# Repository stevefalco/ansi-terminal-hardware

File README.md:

ANSI Terminal is a "dumb" terminal that emulates part of a VT100.  It is sufficient to use with vi under 2.11bsd, and it also works well as a dumb terminal for Linux.  It successfully allows editing using the "vim" editor.  An M68K (M68000) soft-core processor is contained in an FPGA on a CYC1000 module, and handles all the processing chores.

This project contains IP cores as follows:

https://github.com/ijor/fx68k provides the M68000 processor.

https://opencores.org/projects/a_vhd_16550_uart provides a 16550 compatible uart.

Unlike many existing terminal projects, this project targets 1280x1024 monitors, which are much more common than the 640x480 monitors of days gone by.  This also allows higher quality characters, using 16x32 glyphs, rather than the more common 8x16 glyphs.

The terminal supports both hardware and software flow control, as selected by a dip switch, and baud rates from 110 to 115200 are supported.

This project contains the KiCAD schematic, board layout, gerbers, and a 3-D printable case design.  Note that this is a 2-layer board with surface mount components.

A companion project, https://github.com/stevefalco/ansi-terminal-firmware contains the FPGA and assembly language software for the ANSI Terminal.

Here are photos of the case, pcb, schematic and displayed text.  There is a higher resolution copy of the schematic in file terminal.pdf.

ANSI Terminal

(c) 2021 Steven A. Falco

ANSI Terminal is free software: you can redistribute it and/or modify
it under the terms of the GNU General Public License as published by
the Free Software Foundation, either version 3 of the License, or
(at your option) any later version.

ANSI Terminal is distributed in the hope that it will be useful,
but WITHOUT ANY WARRANTY; without even the implied warranty of
MERCHANTABILITY or FITNESS FOR A PARTICULAR PURPOSE.  See the
GNU General Public License for more details.

You should have received a copy of the GNU General Public License
along with ANSI Terminal.  If not, see <https://www.gnu.org/licenses/>.

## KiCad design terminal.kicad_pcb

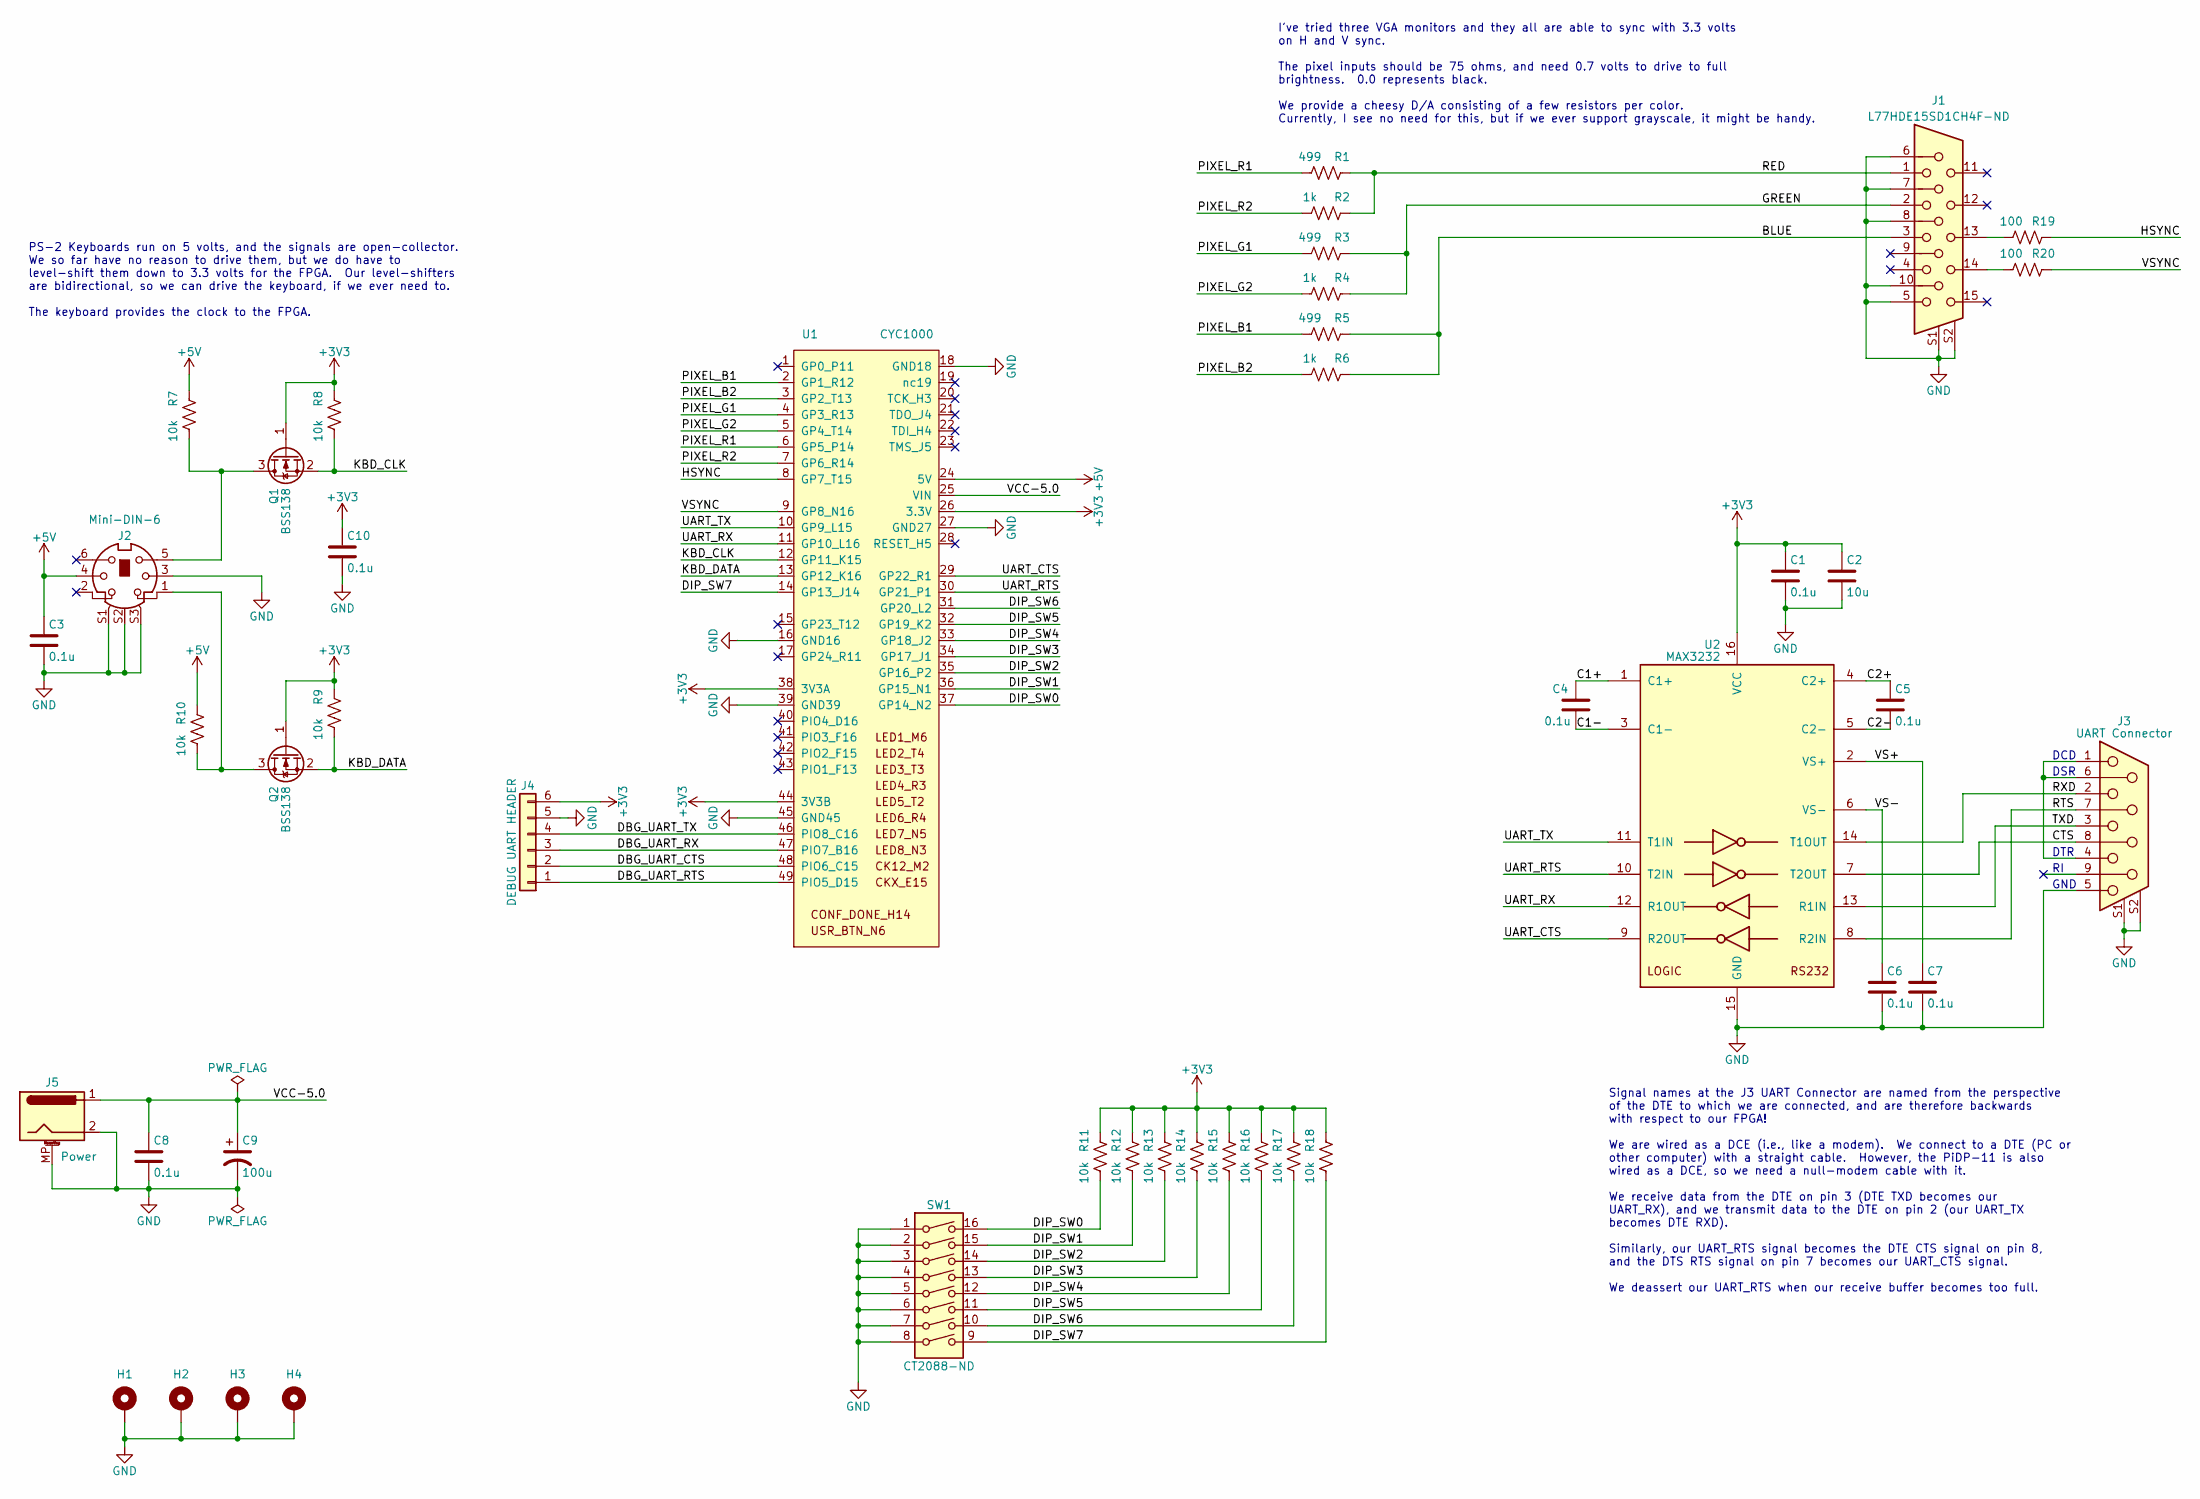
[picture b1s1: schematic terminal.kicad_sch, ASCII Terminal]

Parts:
C1, C3, C4, C5, C6, C7, C8, C10: 0.1u; C_0603_1608Metric_Pad1.08x0.95mm_HandSolder
C2: 10u; C_0603_1608Metric_Pad1.08x0.95mm_HandSolder
C9: 100u; C_1210_3225Metric_Pad1.33x2.70mm_HandSolder
H1, H2, H3, H4: MountingHole_Pad; MountingHole_3.2mm_M3_DIN965_Pad
J1: L77HDE15SD1CH4F-ND; AMPHENOL_L77HDE15SD1CH4F
J2: Mini-DIN-6; CUI_MD-60SM
J3: UART Connector; AMPHENOL_LD09S33E4GX00LF
J4: DEBUG UART HEADER; PinHeader_1x06_P2.54mm_Vertical
J5: Power; BarrelJack_CUI_PJ-063AH_Horizontal
Q1, Q2: BSS138; SOT-23
R1, R3, R5: 499; R_0603_1608Metric_Pad0.98x0.95mm_HandSolder
R2, R4, R6: 1k; R_0603_1608Metric_Pad0.98x0.95mm_HandSolder
R7, R8, R9, R10, R11, R12, R13, R14, R15, R16, R17, R18: 10k; R_0603_1608Metric_Pad0.98x0.95mm_HandSolder
R19, R20: 100; R_0603_1608Metric_Pad0.98x0.95mm_HandSolder
SW1: CT2088-ND; DIP-16_W7.62mm_Socket
U1: CYC1000
U2: MAX3232; TSSOP-16_4.4x5mm_P0.65mm

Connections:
+3V3: C1.1, C2.1, C10.1, J4.6, Q1.1 (G), Q2.1 (G), R8.1, R9.1, R11.1, R12.1, R13.1, R14.1, R15.1, R16.1, R17.1, R18.1, U1.26 (3.3V), U1.38 (3V3A), U1.44 (3V3B), U2.16 (VCC)
+5V: C3.1, J2.4, R7.1, R10.1, U1.24 (5V)
/BLUE: J1.3, R5.1, R6.1
/C1+: C4.1, U2.1 (C1+)
/C1-: C4.2, U2.3 (C1-)
/C2+: C5.1, U2.4 (C2+)
/C2-: C5.2, U2.5 (C2-)
/CTS: J3.8, U2.7 (T2OUT)
/DBG_UART_CTS: J4.2, U1.48 (PIO6_C15)
/DBG_UART_RTS: J4.1, U1.49 (PIO5_D15)
/DBG_UART_RX: J4.3, U1.47 (PIO7_B16)
/DBG_UART_TX: J4.4, U1.46 (PIO8_C16)
/DIP_SW0: R11.2, SW1.16, U1.37 (GP14_N2)
/DIP_SW1: R12.2, SW1.15, U1.36 (GP15_N1)
/DIP_SW2: R13.2, SW1.14, U1.35 (GP16_P2)
/DIP_SW3: R14.2, SW1.13, U1.34 (GP17_J1)
/DIP_SW4: R15.2, SW1.12, U1.33 (GP18_J2)
/DIP_SW5: R16.2, SW1.11, U1.32 (GP19_K2)
/DIP_SW6: R17.2, SW1.10, U1.31 (GP20_L2)
/DIP_SW7: R18.2, SW1.9, U1.14 (GP13_J14)
/GREEN: J1.2, R3.1, R4.1
/HSYNC: R19.1, U1.8 (GP7_T15)
/KBD_CLK: Q1.2 (S), R8.2, U1.12 (GP11_K15)
/KBD_DATA: Q2.2 (S), R9.2, U1.13 (GP12_K16)
/PIXEL_B1: R5.2, U1.2 (GP1_R12)
/PIXEL_B2: R6.2, U1.3 (GP2_T13)
/PIXEL_G1: R3.2, U1.4 (GP3_R13)
/PIXEL_G2: R4.2, U1.5 (GP4_T14)
/PIXEL_R1: R1.2, U1.6 (GP5_P14)
/PIXEL_R2: R2.2, U1.7 (GP6_R14)
/RED: J1.1, R1.1, R2.1
/RTS: J3.7, U2.8 (R2IN)
/RXD: J3.2, U2.14 (T1OUT)
/TXD: J3.3, U2.13 (R1IN)
/UART_CTS: U1.29 (GP22_R1), U2.9 (R2OUT)
/UART_RTS: U1.30 (GP21_P1), U2.10 (T2IN)
/UART_RX: U1.11 (GP10_L16), U2.12 (R1OUT)
/UART_TX: U1.10 (GP9_L15), U2.11 (T1IN)
/VCC-5.0: C8.1, C9.1, J5.1, U1.25 (VIN)
/VS+: C7.1, U2.2 (VS+)
/VS-: C6.1, U2.6 (VS-)
/VSYNC: R20.1, U1.9 (GP8_N16)
GND: C1.2, C2.2, C3.2, C6.2, C7.2, C8.2, C9.2, C10.2, H1.1, H2.1, H3.1, H4.1, J1.5, J1.6, J1.7, J1.8, J1.10, J1.S1, J1.S2, J2.3, J2.S1, J2.S2, J2.S3, J3.5, J3.S1, J3.S2, J4.5, J5.2, J5.MP (MountPin), SW1.1, SW1.2, SW1.3, SW1.4, SW1.5, SW1.6, SW1.7, SW1.8, U1.16 (GND16), U1.18 (GND18), U1.27 (GND27), U1.39 (GND39), U1.45 (GND45), U2.15 (GND)
unnamed: J1.13, R19.2
unnamed: J1.14, R20.2
unnamed: J2.1, Q2.3 (D), R10.2
unnamed: J2.5, Q1.3 (D), R7.2
unnamed: J3.1, J3.4, J3.6

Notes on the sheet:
GND
Signal names at the J3 UART Connector are named from the perspective of the DTE to which we are connected, and are therefore backwards with respect to our FPGA! We are wired as a DCE (i.e., like a modem). We connect to a DTE (PC or other computer) with a straight cable. However, the PiDP-11 is also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
DTR
I've tried three VGA monitors and they all are able to sync with 3.3 volts on H and V sync. The pixel inputs should be 75 ohms, and need 0.7 volts to drive to full brightness. 0.0 represents black. We provide a cheesy D/A consisting of a few resistors per color. Currently, I see no need for this, b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
PS-2 Keyboards run on 5 volts, and the signals are open-collector. We so far have no reason to drive them, but we do have to level-shift them down to 3.3 volts for the FPGA. Our level-shifters are bidirectional, so we can drive the keyboard, if we ever need to. The keyboard provides the clock to th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
DCD
DSR

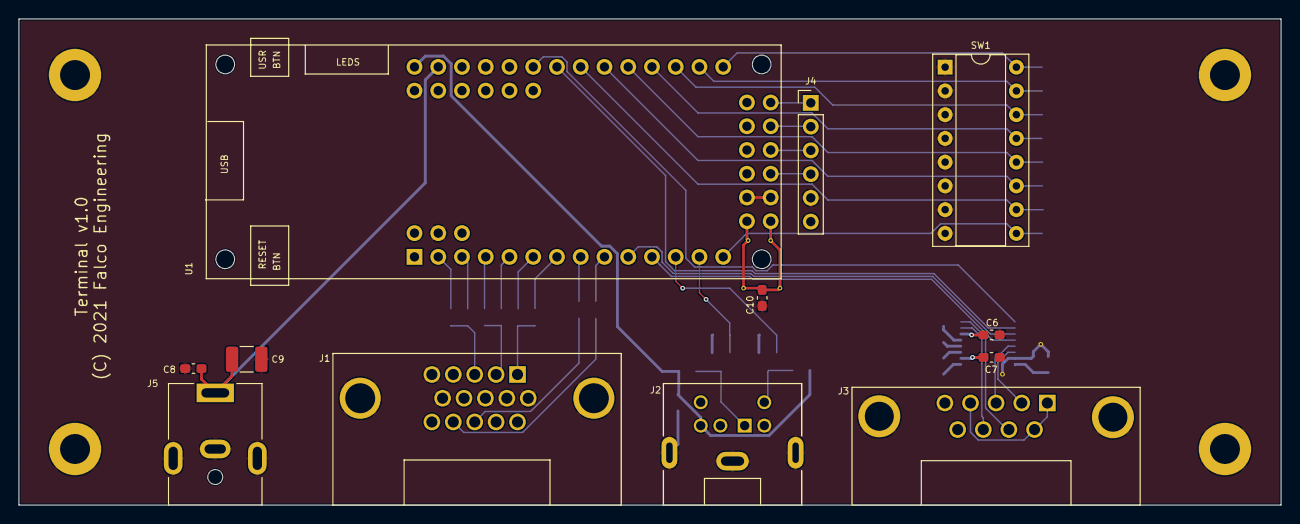
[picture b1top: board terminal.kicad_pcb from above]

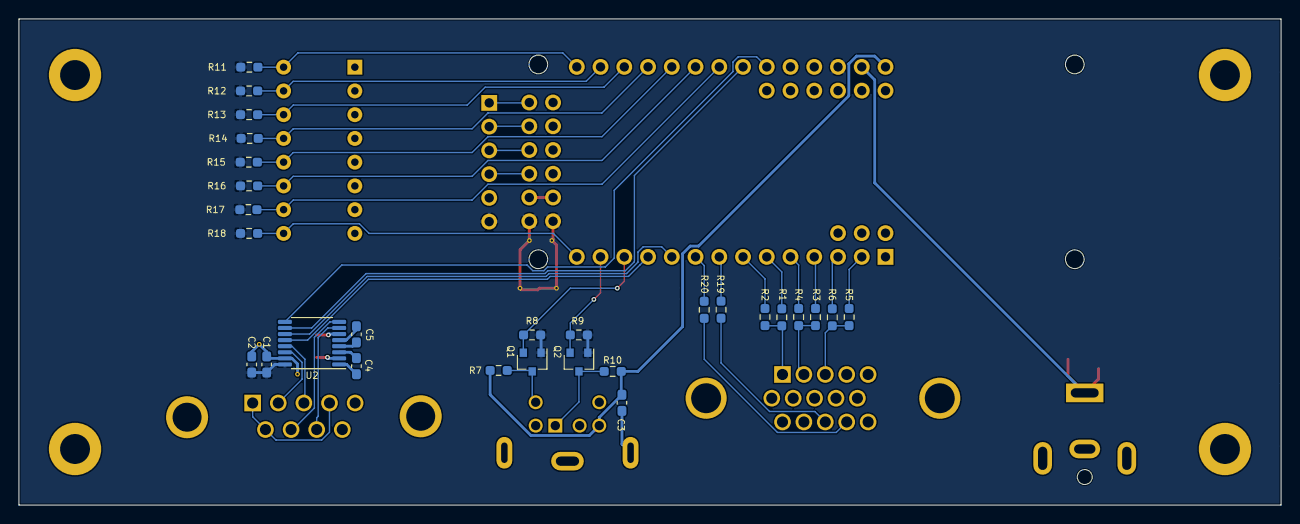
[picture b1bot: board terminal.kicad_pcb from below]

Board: 2 copper layers, 135.0 x 52.0 mm, 44 parts (28 on the bottom side), 48 nets.

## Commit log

2021-03-11 Initial
2021-03-11 Schematic complete
2021-03-12 Starting layout
2021-03-12 Wiring connectors
2021-03-12 Should be pretty close
2021-03-13 V1 looks good
2021-03-13 Add BOM
2021-03-16 Sense of RX/TX and CTS/RTS were backwards.
    Fortunately, that is easy to fix in the FPGA by remapping the signals to
    different pins.
2021-03-26 Fix R values & silk
2021-03-28 Add housing
2021-04-15 Housing update
2021-04-18 Add README.md
2021-04-18 Add pictures
2021-04-18 Add readme
2021-04-18 Typo in README
2021-04-19 Add schematic pdf
2021-04-19 Add photos
2021-04-19 Mention cores used
2021-04-19 Crosslink projects
2021-11-21 Convert to KiCad 6 series
2021-11-24 Move to KiCad 6
2021-12-31 Move template file
2025-07-10 Cache update

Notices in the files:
terminal.kicad_pcb:
(C) 2021 Falco Engineering
